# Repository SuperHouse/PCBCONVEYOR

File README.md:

PCB Conveyor Belt
=================

Copyright 2021 SuperHouse Automation Pty Ltd  www.superhouse.tv

THIS IS VERY PRELIMINARY! I'm adding this work-in-progress to GitHub
so that Seon can access it, but it's not in a ready state for
general consumption.
^^^^^^^^^^^^^^^^^^^^^^^^^^^^^^^^^^^^^^^^^^^^^^^^^^^^^^^^^^^^^^^

A conveyor belt for linking together PCB assembly machines, including
pick-and-place, reflow, optical inspection, etc.

The width of the belt is adjustable to suit different sizes of PCBs
and panels. This project includes the design for the mechanical
structure, a controller, and firmware for the controller.

More information:

  http://www.superhouse.tv/pcbconveyor

INSTALLATION
------------
The "Hardware" directory contains the PCB design as an EAGLE project.
This can be imported into KiCAD, or opened natively using Fusion360.

CREDITS
-------
Designed by Jonathan Oxer jon@oxer.com.au

DISTRIBUTION
------------
The specific terms of distribution of this project are governed by the
license referenced below.

LICENSE
-------
Licensed under the TAPR Open Hardware License (www.tapr.org/OHL).
The "license" folder within this repository also contains a copy of
this license in plain text format.

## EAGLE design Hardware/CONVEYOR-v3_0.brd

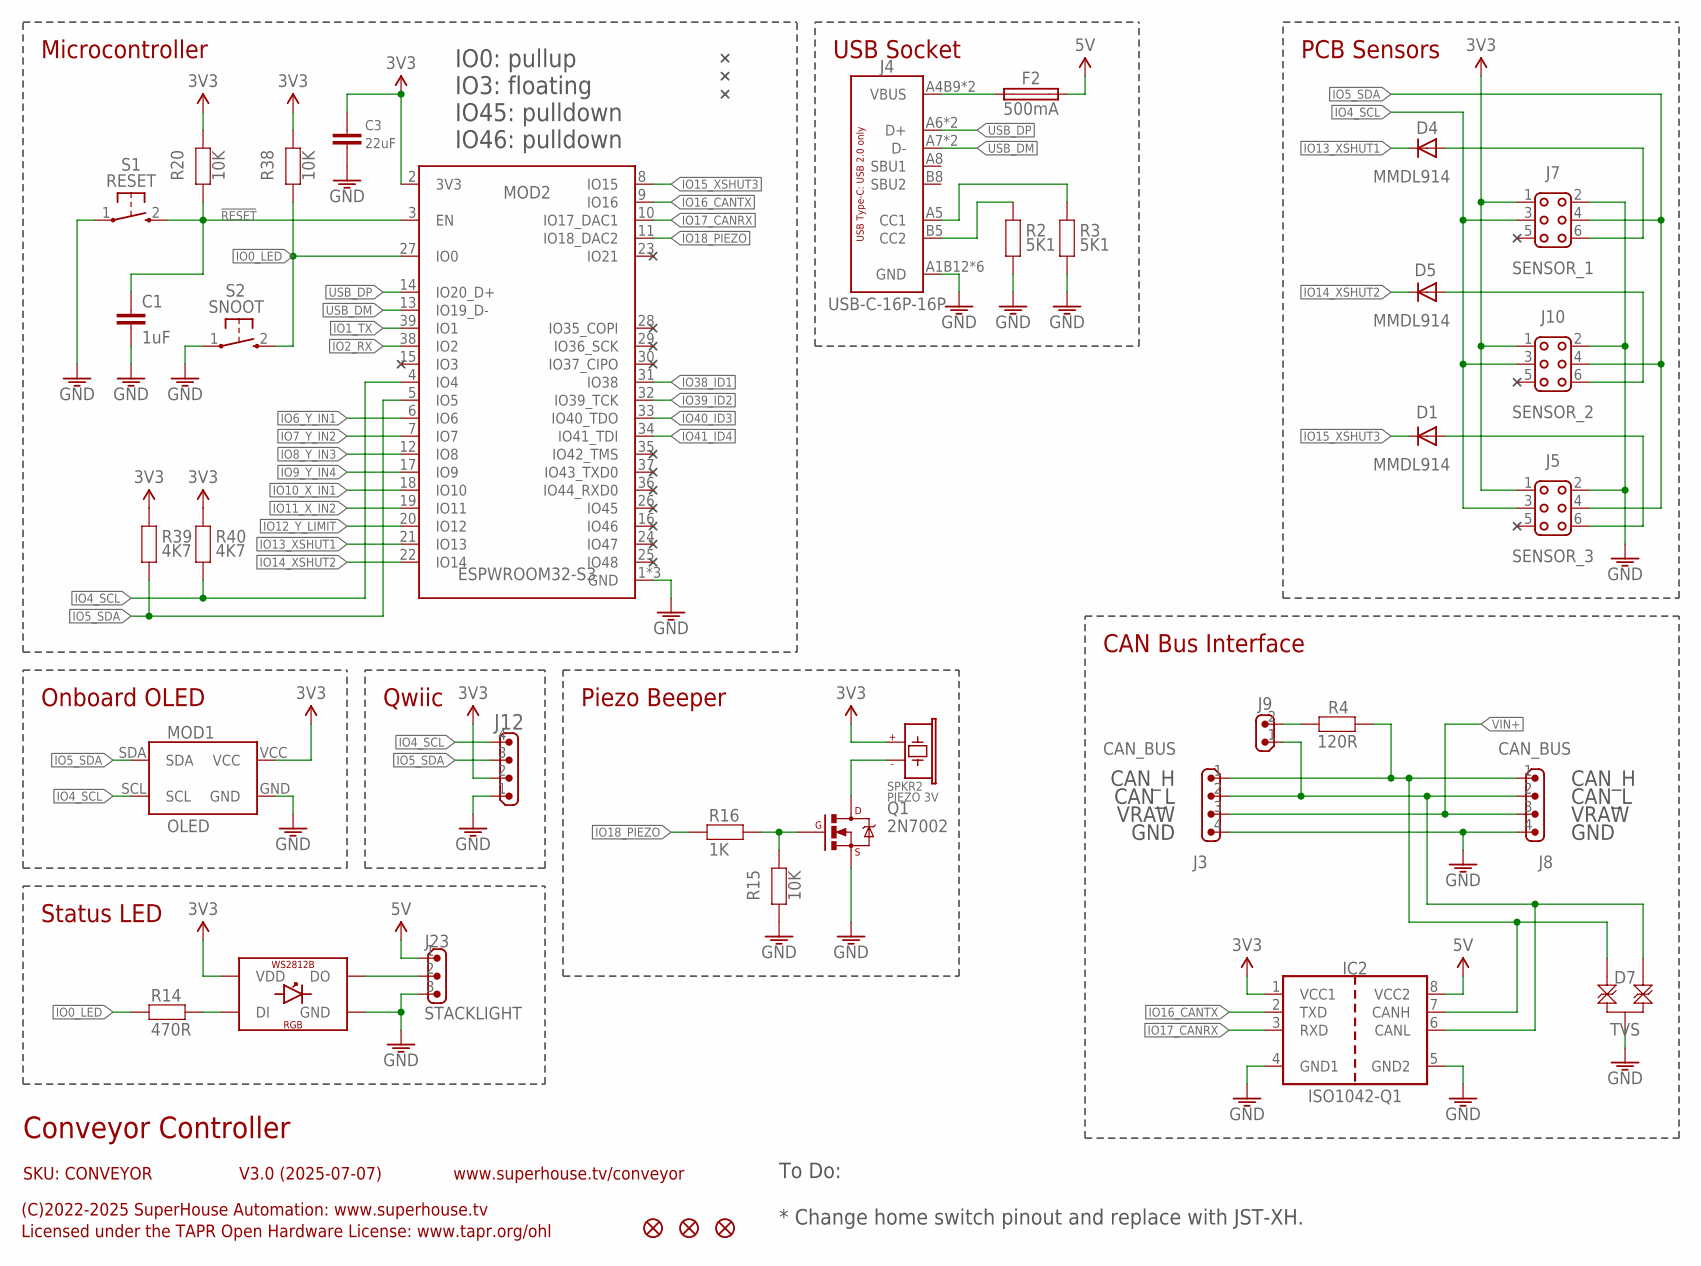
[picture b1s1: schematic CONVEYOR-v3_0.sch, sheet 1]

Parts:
C1: 1uF; C0603
C3: 22uF; C0805
D1, D4, D5: MMDL914; SOD-123
D7: TVS; SOT23-3
F2: 500mA; 1206
IC2: ISO1042-Q1; SO08-W
J3, J8: CAN_BUS; SCREWTERMINAL-3.81MM-PLUGGABLE-HOR-4
J4: USB-C-16P-16P; USB-C-16P
J5: SENSOR_3; 2X3-2.54-SHROUDED
J7: SENSOR_1; 2X3-2.54-SHROUDED
J9: M02-PIN-JUMP-Y; 1X02-P-JUMP-Y
J10: SENSOR_2; 2X3-2.54-SHROUDED
J12: M04-SM4B-SH; JST-SM4B-SH
J23: STACKLIGHT; 1X03
LED2: WS2812B-PTH5MM; 5MM4PIN
MOD1: OLED; OLED-128X32-0.91-HEADER
MOD2: ESPWROOM32-S3
Q1: 2N7002; SOT23-3
R2, R3: 5K1; R0603
R4: 120R; R2010
R14: 470R; R0603
R15, R20, R38: 10K; R0603
R16: 1K; R0603
R39, R40: 4K7; R0603
S1: RESET; TACTILE_SMT_3X4X2
S2: SNOOT; TACTILE_SMT_3X4X2
SPKR2: PIEZO 3V; PIEZO-9.6X9.6-SMT
U$4, U$5, U$6: FIDUCIAL1X2.5; FIDUCIAL-1X2.5

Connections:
3.3V: C3.1, IC2.1 (VCC1), J5.1, J7.1, J10.1, J12.2, LED2.2 (VDD), MOD1.VCC, MOD2.2 (3V3), R20.1, R38.1, R39.1, R40.1, SPKR2.1 (+); also elsewhere on the board
5V: F2.2, IC2.8 (VCC2), J23.1; also elsewhere on the board
!RESET: C1.1, MOD2.3 (EN), R20.2, S1.2 (S)
CAN_H1: D7.2, IC2.7 (CANH), J3.1, J8.1, R4.2
CAN_L1: D7.1, IC2.6 (CANL), J3.2, J8.2, J9.1
GND: C1.2, C3.2, D7.3, IC2.4 (GND1), IC2.5 (GND2), J3.4, J4.A1B12 (GND), J4.A12B1 (GND), J4.FIX1 (GND), J4.FIX2 (GND), J4.FIX3 (GND), J4.FIX4 (GND), J5.2, J7.2, J8.4, J10.2, J12.1, J23.3, LED2.3 (GND), MOD1.GND, MOD2.1 (GND), MOD2.40 (GND), MOD2.41 (GND), Q1.2 (S), R2.2, R3.2, R15.2, S1.1, S2.1; also elsewhere on the board
IO0_LED: MOD2.27 (IO0), R14.1, R38.2, S2.2 (S)
IO1_TX: MOD2.39 (IO1)
IO2_RX: MOD2.38 (IO2)
IO4_SCL: J5.3, J7.3, J10.3, J12.4, MOD1.SCL, MOD2.4 (IO4), R40.2
IO5_SDA: J5.4, J7.4, J10.4, J12.3, MOD1.SDA, MOD2.5 (IO5), R39.2
IO6_Y_IN1: MOD2.6 (IO6); also elsewhere on the board
IO7_Y_IN2: MOD2.7 (IO7); also elsewhere on the board
IO8_Y_IN3: MOD2.12 (IO8); also elsewhere on the board
IO9_Y_IN4: MOD2.17 (IO9); also elsewhere on the board
IO10_X_IN1: MOD2.18 (IO10); also elsewhere on the board
IO11_X_IN2: MOD2.19 (IO11); also elsewhere on the board
IO12_Y_LIMIT: MOD2.20 (IO12); also elsewhere on the board
IO13_XSHUT1: D4.1 (C), MOD2.21 (IO13)
IO14_XSHUT2: D5.1 (C), MOD2.22 (IO14)
IO15_XSHUT3: D1.1 (C), MOD2.8 (IO15)
IO16_CANTX: IC2.2 (TXD), MOD2.9 (IO16)
IO17_CANRX: IC2.3 (RXD), MOD2.10 (IO17_DAC1)
IO18_PIEZO: MOD2.11 (IO18_DAC2), R16.1
IO38_ID1: MOD2.31 (IO38); also elsewhere on the board
IO39_ID2: MOD2.32 (IO39_TCK); also elsewhere on the board
IO40_ID3: MOD2.33 (IO40_TDO); also elsewhere on the board
IO41_ID4: MOD2.34 (IO41_TDI); also elsewhere on the board
IO46: MOD2.16 (IO46)
unnamed: J9.2, R4.1
unnamed: LED2.4 (DI), R14.2
unnamed: D1.2 (A), J5.6
unnamed: J4.B5 (CC2), R2.1
unnamed: J4.A5 (CC1), R3.1
unnamed: F2.1, J4.A4B9 (VBUS), J4.A9B4 (VBUS)
unnamed: J23.2, LED2.1 (DO)
unnamed: D5.2 (A), J10.6
unnamed: Q1.1 (G), R15.1, R16.2
unnamed: Q1.3 (D), SPKR2.2 (-)
unnamed: D4.2 (A), J7.6
USB_DM: J4.A7 (D-), J4.B7 (D-), MOD2.13 (IO19_D-)
USB_DP: J4.A6 (D+), J4.B6 (D+), MOD2.14 (IO20_D+)
VIN+: J3.3, J8.3; also elsewhere on the board

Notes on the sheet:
Conveyor Controller
SKU: CONVEYOR
(C)2022-2025 SuperHouse Automation: www.superhouse.tv
Licensed under the TAPR Open Hardware License: www.tapr.org/ohl
www.superhouse.tv/conveyor
V3.0 (2025-07-07)
To Do: * Change home switch pinout and replace with JST-XH.
Piezo Beeper
Microcontroller
Qwiic
IO0: pullup IO3: floating IO45: pulldown IO46: pulldown
Status LED
PCB Sensors
Onboard OLED
USB Socket
CAN Bus Interface
CAN_H
CAN_L
GND
VRAW

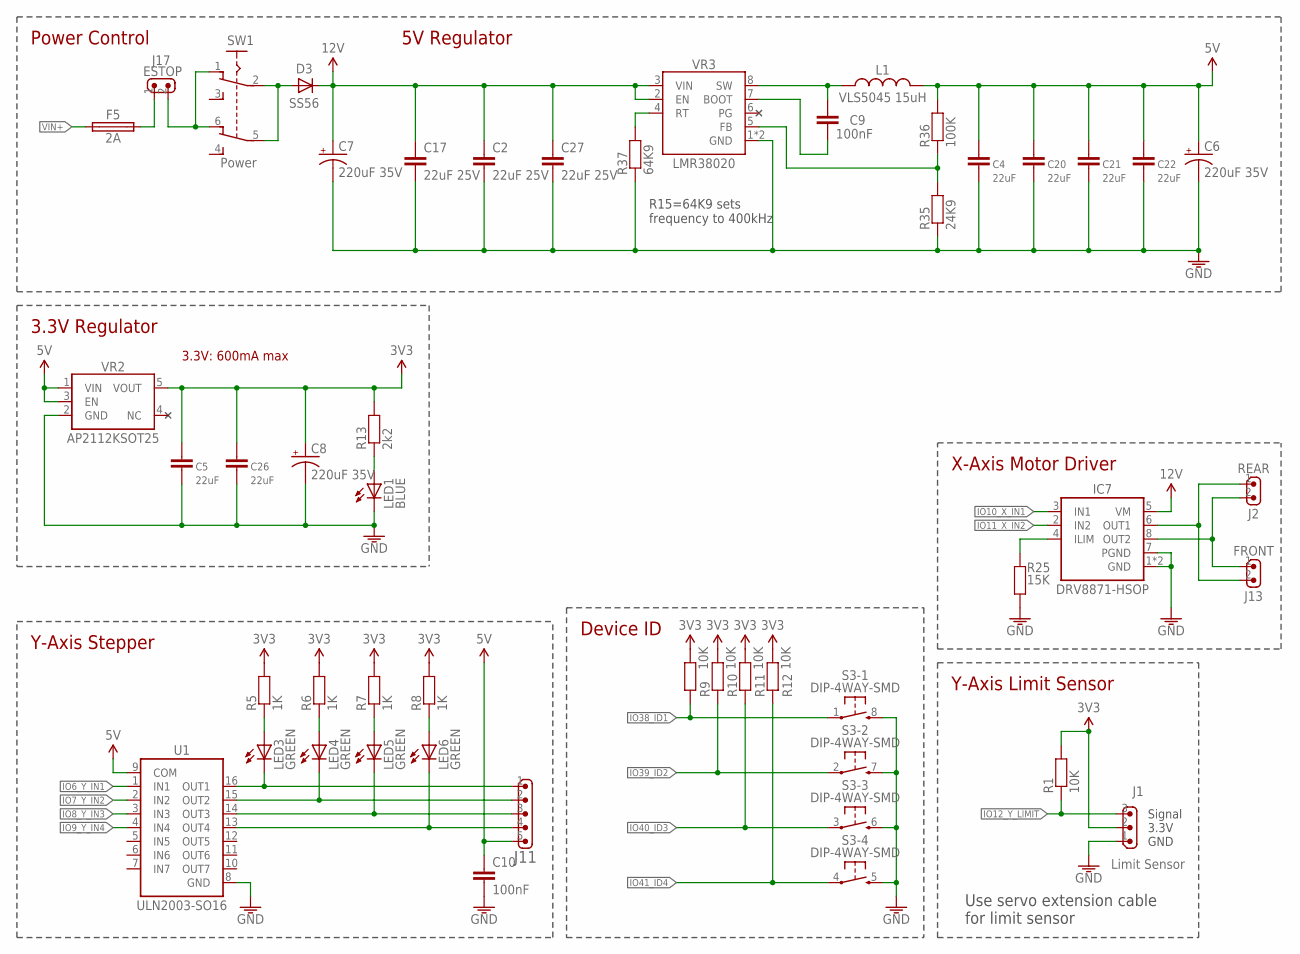
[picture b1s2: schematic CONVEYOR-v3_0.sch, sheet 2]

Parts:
C2, C17, C27: 22uF 25V; C0805
C4, C5, C20, C21, C22, C26: 22uF; C0805
C6, C7, C8: 220uF 35V; PANASONIC_G
C9, C10: 100nF; C0603
D3: SS56; SMA-DIODE
F5: 2A; OMNIBLOK
IC7: DRV8871-HSOP; SOIC8T
J1: Limit Sensor; 1X03-P
J2: REAR; JST-B2B-XH-A
J11: M05-B5B-XH; JST-B5B-XH-A
J13: FRONT; JST-B2B-XH-A
J17: ESTOP; SCREWTERMINAL-3.81MM-PLUGGABLE-HOR-2
L1: VLS5045 15uH; INDUCTOR-5045
LED1: BLUE; LED-0603
LED3, LED4, LED5, LED6: GREEN; LED-0603
R1, R9, R10, R11, R12: 10K; R0603
R5, R6, R7, R8: 1K; R0603
R13: 2k2; R0603
R25: 15K; R0603
R35: 24K9; R0603
R36: 100K; R0603
R37: 64K9; R0603
S3: DIP-4WAY-SMD; DIP-8-SMD
SW1: Power; 7201SD9AV2BE
U1: ULN2003-SO16; SO16
VR2: AP2112KSOT25; SOT23-5
VR3: LMR38020; HSOIC8

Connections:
3.3V: C5.1, C8.+, C26.1, J1.2, R1.2, R5.2, R6.2, R7.2, R8.2, R9.2, R10.2, R11.2, R12.2, R13.2, VR2.5 (VOUT); also elsewhere on the board
5V: C4.1, C6.+, C10.1, C20.1, C21.1, C22.1, J11.5, L1.2, R36.2, U1.9 (COM), VR2.1 (VIN), VR2.3 (EN); also elsewhere on the board
12V: C2.1, C7.+, C17.1, C27.1, D3.C, IC7.5 (VM), VR3.2 (EN), VR3.3 (VIN)
GND: C2.2, C4.2, C5.2, C6.-, C7.-, C8.-, C10.2, C17.2, C20.2, C21.2, C22.2, C26.2, C27.2, IC7.1 (GND), IC7.7 (PGND), IC7.TGND (GND), J1.1, LED1.C, R25.1, R35.1, R37.1, S3.5 (S), S3.6 (S), S3.7 (S), S3.8 (S), U1.8 (GND), VR2.2 (GND), VR3.1 (GND), VR3.TGND (GND); also elsewhere on the board
IO6_Y_IN1: U1.1 (IN1); also elsewhere on the board
IO7_Y_IN2: U1.2 (IN2); also elsewhere on the board
IO8_Y_IN3: U1.3 (IN3); also elsewhere on the board
IO9_Y_IN4: U1.4 (IN4); also elsewhere on the board
IO10_X_IN1: IC7.3 (IN1); also elsewhere on the board
IO11_X_IN2: IC7.2 (IN2); also elsewhere on the board
IO12_Y_LIMIT: J1.3, R1.1; also elsewhere on the board
IO38_ID1: R9.1, S3.1; also elsewhere on the board
IO39_ID2: R10.1, S3.2; also elsewhere on the board
IO40_ID3: R11.1, S3.3; also elsewhere on the board
IO41_ID4: R12.1, S3.4; also elsewhere on the board
unnamed: J17.2, SW1.1, SW1.6
unnamed: IC7.4 (ILIM), R25.2
unnamed: F5.2, J17.1
unnamed: D3.A, SW1.2, SW1.5
unnamed: LED3.A, R5.1
unnamed: J11.1, LED3.C, U1.16 (OUT1)
unnamed: LED4.A, R6.1
unnamed: LED5.A, R7.1
unnamed: LED6.A, R8.1
unnamed: J11.2, LED4.C, U1.15 (OUT2)
unnamed: J11.3, LED5.C, U1.14 (OUT3)
unnamed: J11.4, LED6.C, U1.13 (OUT4)
unnamed: IC7.6 (OUT1), J2.1, J13.2
unnamed: IC7.8 (OUT2), J2.2, J13.1
unnamed: LED1.A, R13.1
unnamed: C9.1, L1.1, VR3.8 (SW)
unnamed: R37.2, VR3.4 (RT)
unnamed: R35.2, R36.1, VR3.5 (FB)
unnamed: C9.2, VR3.7 (BOOT)
PG: VR3.6 (PG)
VIN+: F5.1; also elsewhere on the board

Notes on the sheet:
3.3V: 600mA max
5V Regulator
3.3V Regulator
R15=64K9 sets frequency to 400kHz
Power Control
Y-Axis Stepper
Device ID
3.3V
Signal
GND
Use servo extension cable for limit sensor
Y-Axis Limit Sensor
X-Axis Motor Driver

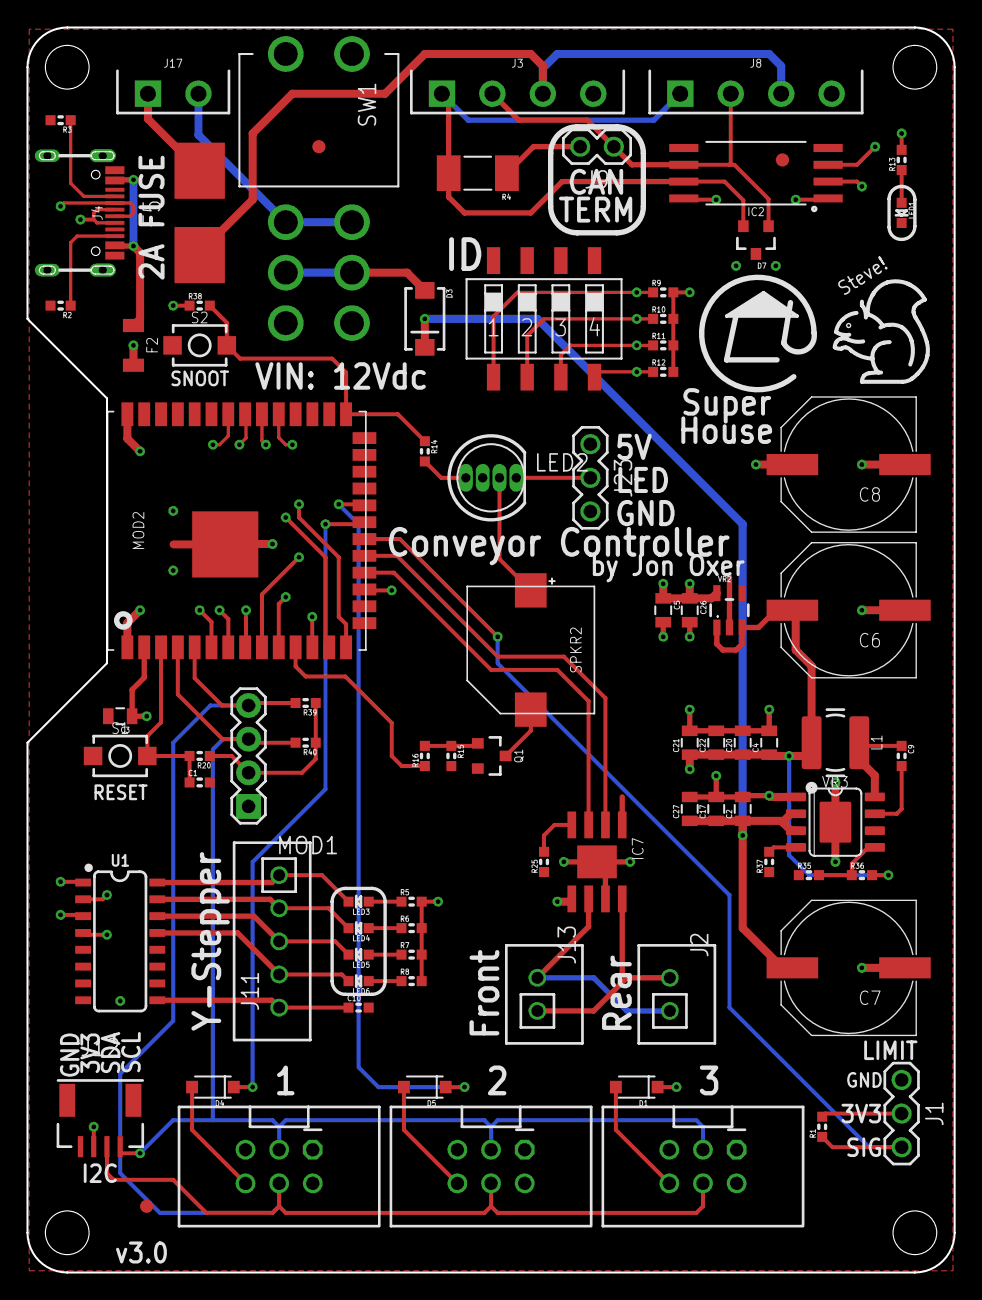
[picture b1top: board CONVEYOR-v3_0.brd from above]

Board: 4 copper layers, 70.0 x 94.0 mm, 84 parts (0 on the bottom side), 60 nets.

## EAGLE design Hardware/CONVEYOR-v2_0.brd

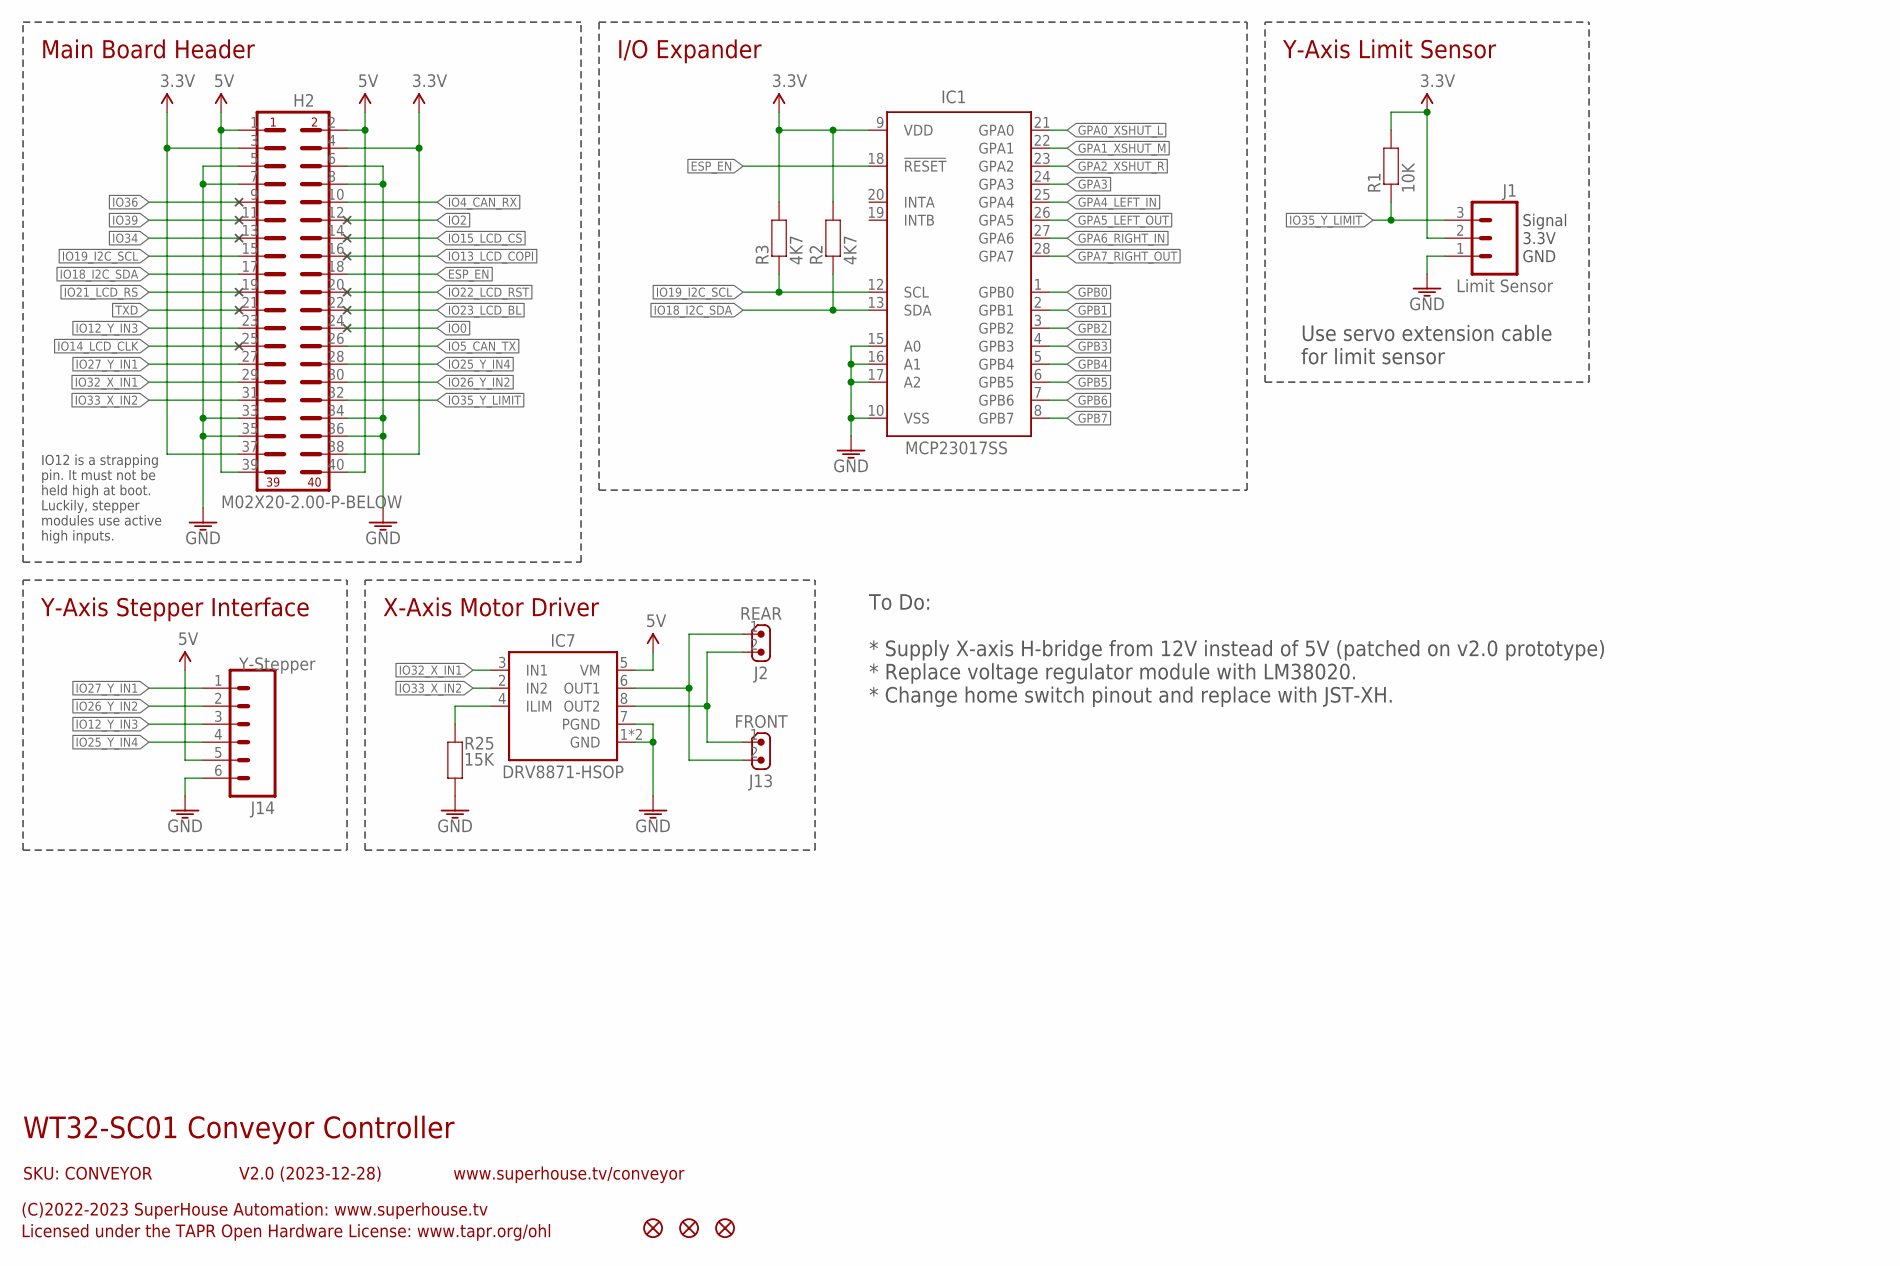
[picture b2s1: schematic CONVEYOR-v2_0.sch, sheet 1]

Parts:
H2: M02X20-2.00-P-BELOW; 2X20-2.00-P-BELOW
IC1: MCP23017SS; SSOP28
IC7: DRV8871-HSOP; SOIC8T
J1: Limit Sensor; 1X03-P
J2: REAR; JST-B2B-XH-A
J13: FRONT; JST-B2B-XH-A
J14: Y-Stepper; JST-B6B-XH-A
R1: 10K; R0603
R2, R3: 4K7; R0603
R25: 15K; R0603
U$4, U$5, U$6: FIDUCIAL1X2.5; FIDUCIAL-1X2.5

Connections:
3.3V: H2.3, H2.4, H2.37, H2.38, IC1.9 (VDD), J1.2, R1.2, R2.2, R3.2; also elsewhere on the board
5V: H2.1, H2.2, H2.39, H2.40, IC7.5 (VM), J14.5; also elsewhere on the board
ESP_EN: H2.18, IC1.18 (!RESET)
GND: H2.5, H2.6, H2.7, H2.8, H2.33, H2.34, H2.35, H2.36, IC1.10 (VSS), IC1.15 (A0), IC1.16 (A1), IC1.17 (A2), IC7.1 (GND), IC7.7 (PGND), IC7.TGND (GND), J1.1, J14.6, R25.1; also elsewhere on the board
GPA0_XSHUT_L: IC1.21 (GPA0); also elsewhere on the board
GPA1_XSHUT_M: IC1.22 (GPA1); also elsewhere on the board
GPA2_XSHUT_R: IC1.23 (GPA2); also elsewhere on the board
GPA3: IC1.24 (GPA3)
GPA4_LEFT_IN: IC1.25 (GPA4); also elsewhere on the board
GPA5_LEFT_OUT: IC1.26 (GPA5); also elsewhere on the board
GPA6_RIGHT_IN: IC1.27 (GPA6); also elsewhere on the board
GPA7_RIGHT_OUT: IC1.28 (GPA7); also elsewhere on the board
GPB0: IC1.1 (GPB0)
GPB1: IC1.2 (GPB1)
GPB2: IC1.3 (GPB2)
GPB3: IC1.4 (GPB3)
GPB4: IC1.5 (GPB4)
GPB5: IC1.6 (GPB5)
GPB6: IC1.7 (GPB6)
GPB7: IC1.8 (GPB7)
IO0: H2.24
IO2: H2.12
IO4_CAN_RX: H2.10; also elsewhere on the board
IO5_CAN_TX: H2.26; also elsewhere on the board
IO12_Y_IN3: H2.23, J14.3
IO13_LCD_COPI: H2.16
IO14_LCD_CLK: H2.25
IO15_LCD_CS: H2.14
IO18_I2C_SDA: H2.17, IC1.13 (SDA), R2.1; also elsewhere on the board
IO19_I2C_SCL: H2.15, IC1.12 (SCL), R3.1; also elsewhere on the board
IO21_LCD_RS: H2.19
IO22_LCD_RST: H2.20
IO23_LCD_BL: H2.22
IO25_Y_IN4: H2.28, J14.4
IO26_Y_IN2: H2.30, J14.2
IO27_Y_IN1: H2.27, J14.1
IO32_X_IN1: H2.29, IC7.3 (IN1)
IO33_X_IN2: H2.31, IC7.2 (IN2)
IO34: H2.13
IO35_Y_LIMIT: H2.32, J1.3, R1.1
IO36: H2.9
IO39: H2.11
unnamed: IC7.4 (ILIM), R25.2
unnamed: IC7.6 (OUT1), J2.1, J13.2
unnamed: IC7.8 (OUT2), J2.2, J13.1
TXD: H2.21

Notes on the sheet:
WT32-SC01 Conveyor Controller
SKU: CONVEYOR
(C)2022-2023 SuperHouse Automation: www.superhouse.tv
Licensed under the TAPR Open Hardware License: www.tapr.org/ohl
www.superhouse.tv/conveyor
V2.0 (2023-12-28)
Y-Axis Stepper Interface
Main Board Header
I/O Expander
3.3V
Signal
GND
Use servo extension cable for limit sensor
Y-Axis Limit Sensor
IO12 is a strapping pin. It must not be held high at boot. Luckily, stepper modules use active high inputs.
X-Axis Motor Driver
To Do: * Supply X-axis H-bridge from 12V instead of 5V (patched on v2.0 prototype) * Replace voltage regulator module with LM38020. * Change home switch pinout and replace with JST-XH.

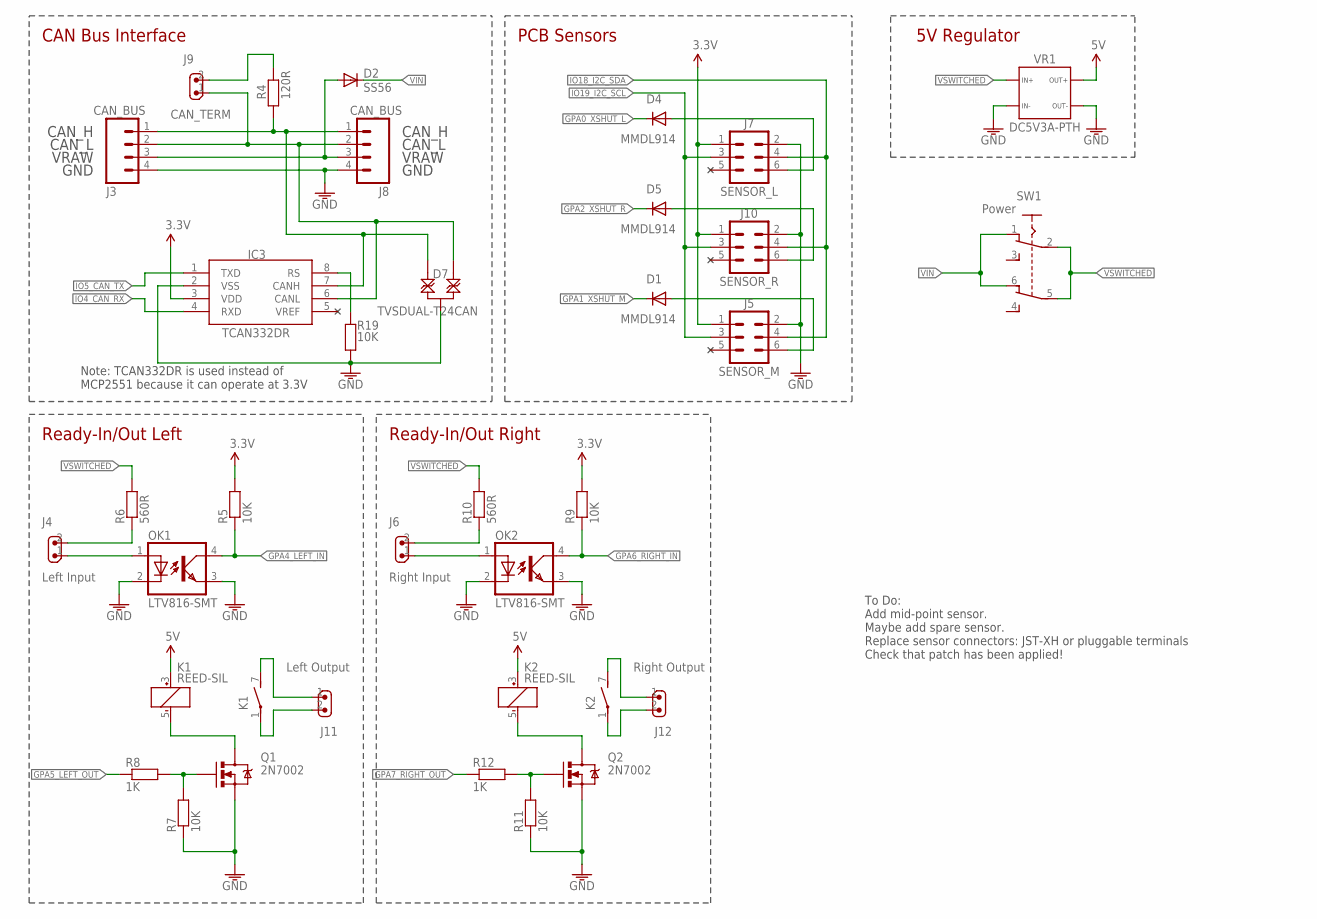
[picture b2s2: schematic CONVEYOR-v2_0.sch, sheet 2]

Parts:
D1, D4, D5: MMDL914; SOD-323
D2: SS56; SMA-DIODE
D7: TVSDUAL-T24CAN; SOT23-3
IC3: TCAN332DR; SO08
J3, J8: CAN_BUS; SCREWTERMINAL-3.81MM-VERT-4
J4: Left Input; 1X02-KF2510
J5: SENSOR_M; 2X3-2.54-SHROUDED
J6: Right Input; 1X02-KF2510
J7: SENSOR_L; 2X3-2.54-SHROUDED
J9: CAN_TERM; 1X02-P-JUMP-Y
J10: SENSOR_R; 2X3-2.54-SHROUDED
J11: Left Output; 1X02-KF2510
J12: Right Output; 1X02-KF2510
K1, K2: REED-SIL; REED
OK1, OK2: LTV816-SMT; SMD4
Q1, Q2: 2N7002; SOT23-3
R4: 120R; R2010
R5, R7, R9, R11, R19: 10K; R0603
R6, R10: 560R; R0603
R8, R12: 1K; R0603
SW1: Power; 7201SD9AV2BE
VR1: DC5V3A-PTH

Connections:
3.3V: IC3.3 (VDD), J5.1, J7.1, J10.1, R5.2, R9.2; also elsewhere on the board
5V: K1.3 (+), K2.3 (+), VR1.3A (3), VR1.3B (3); also elsewhere on the board
CAN_H1: D7.2, IC3.7 (CANH), J3.1, J8.1, R4.1
CAN_L1: D7.1, IC3.6 (CANL), J3.2, J8.2, J9.1
CAN_VIN: D2.A, J3.3, J8.3
GND: D7.3, IC3.2 (VSS), J3.4, J5.2, J7.2, J8.4, J10.2, OK1.2 (C), OK1.3 (EMIT), OK2.2 (C), OK2.3 (EMIT), Q1.2 (S), Q2.2 (S), R7.1, R11.1, R19.1, VR1.1A (1), VR1.1B (1), VR1.4A (4), VR1.4B (4); also elsewhere on the board
GPA0_XSHUT_L: D4.1 (C); also elsewhere on the board
GPA1_XSHUT_M: D1.1 (C); also elsewhere on the board
GPA2_XSHUT_R: D5.1 (C); also elsewhere on the board
GPA4_LEFT_IN: OK1.4 (COL), R5.1; also elsewhere on the board
GPA5_LEFT_OUT: R8.1; also elsewhere on the board
GPA6_RIGHT_IN: OK2.4 (COL), R9.1; also elsewhere on the board
GPA7_RIGHT_OUT: R12.1; also elsewhere on the board
IO4_CAN_RX: IC3.4 (RXD); also elsewhere on the board
IO5_CAN_TX: IC3.1 (TXD); also elsewhere on the board
IO18_I2C_SDA: J5.4, J7.4, J10.4; also elsewhere on the board
IO19_I2C_SCL: J5.3, J7.3, J10.3; also elsewhere on the board
unnamed: IC3.8 (RS), R19.2
unnamed: D1.2 (A), J5.6
unnamed: J9.2, R4.2
unnamed: D5.2 (A), J10.6
unnamed: J4.1, OK1.1 (A)
unnamed: J4.2, R6.1
unnamed: D4.2 (A), J7.6
unnamed: K1.5 (-), Q1.3 (D)
unnamed: J11.2, K1.1
unnamed: Q1.1 (G), R7.2, R8.2
unnamed: J11.1, K1.7 (S)
unnamed: Q2.1 (G), R11.2, R12.2
unnamed: K2.5 (-), Q2.3 (D)
unnamed: J12.2, K2.1
unnamed: J12.1, K2.7 (S)
unnamed: J6.1, OK2.1 (A)
unnamed: J6.2, R10.1
VIN: D2.C, SW1.1, SW1.6
VSWITCHED: R6.2, R10.2, SW1.2, SW1.5, VR1.2A (2), VR1.2B (2)

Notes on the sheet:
5V Regulator
CAN Bus Interface
Note: TCAN332DR is used instead of MCP2551 because it can operate at 3.3V
CAN_H
CAN_L
GND
VRAW
PCB Sensors
Ready-In/Out Left
Ready-In/Out Right
To Do: Add mid-point sensor. Maybe add spare sensor. Replace sensor connectors: JST-XH or pluggable terminals Check that patch has been applied!

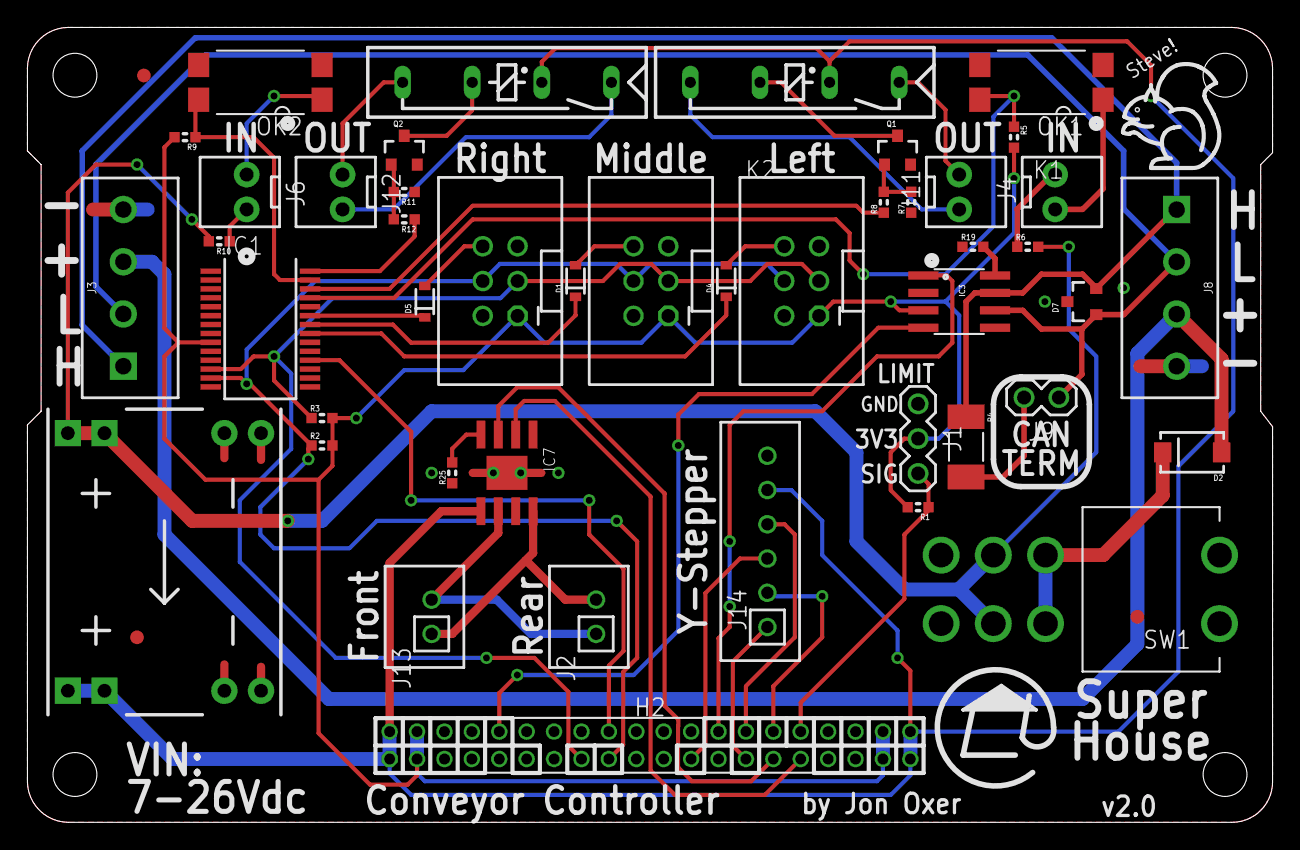
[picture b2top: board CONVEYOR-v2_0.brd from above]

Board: 2 copper layers, 90.9 x 58.0 mm, 48 parts (0 on the bottom side), 47 nets.

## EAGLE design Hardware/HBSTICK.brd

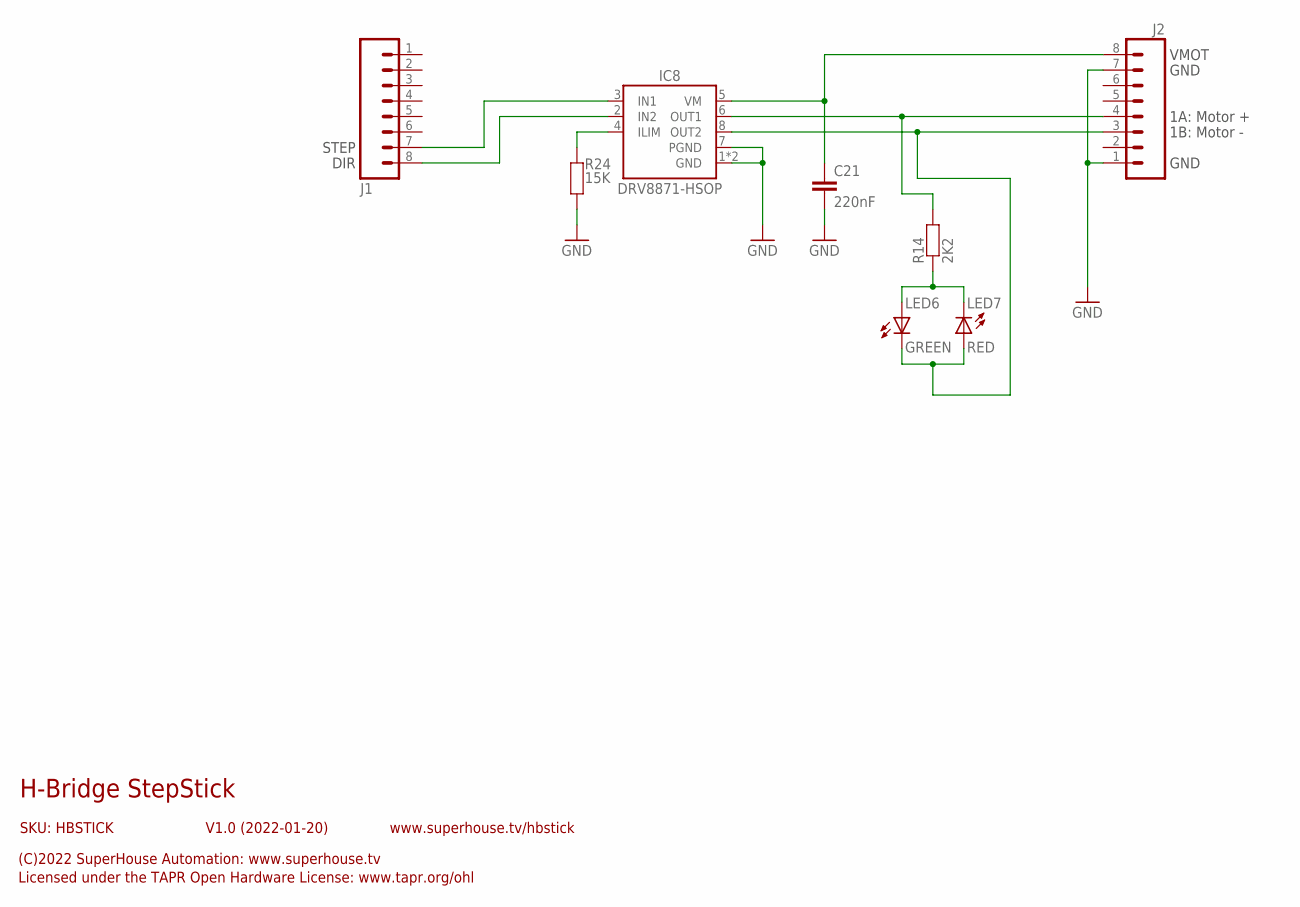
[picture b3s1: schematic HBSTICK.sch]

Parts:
C21: 220nF; C0603
IC8: DRV8871-HSOP; SOIC8T
J1, J2: M08-PIN-BELOW; 1X08-P-BELOW
LED6: GREEN; LED-0603
LED7: RED; LED-0603
R14: 2K2; R0603
R24: 15K; R0603

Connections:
GND: C21.2, IC8.1 (GND), IC8.7 (PGND), IC8.TGND (GND), J2.1, J2.7, R24.1
MOTOR+: IC8.6 (OUT1), J2.4, R14.2
MOTOR-: IC8.8 (OUT2), J2.3, LED6.C, LED7.A
unnamed: IC8.2 (IN2), J1.8
unnamed: IC8.3 (IN1), J1.7
unnamed: LED6.A, LED7.C, R14.1
unnamed: IC8.4 (ILIM), R24.2
VIN+: C21.1, IC8.5 (VM), J2.8

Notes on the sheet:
H-Bridge StepStick
SKU: HBSTICK
(C)2022 SuperHouse Automation: www.superhouse.tv
Licensed under the TAPR Open Hardware License: www.tapr.org/ohl
www.superhouse.tv/hbstick
V1.0 (2022-01-20)
VMOT
GND
1A: Motor +
1B: Motor -
STEP
DIR

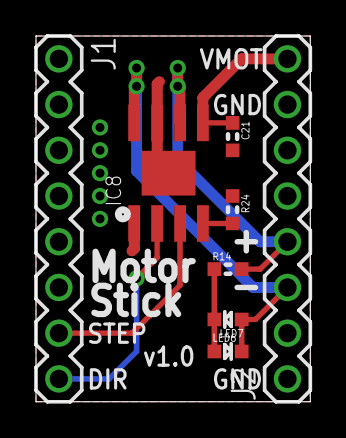
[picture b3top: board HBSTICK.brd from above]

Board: 2 copper layers, 15.2 x 20.3 mm, 8 parts (0 on the bottom side), 8 nets.

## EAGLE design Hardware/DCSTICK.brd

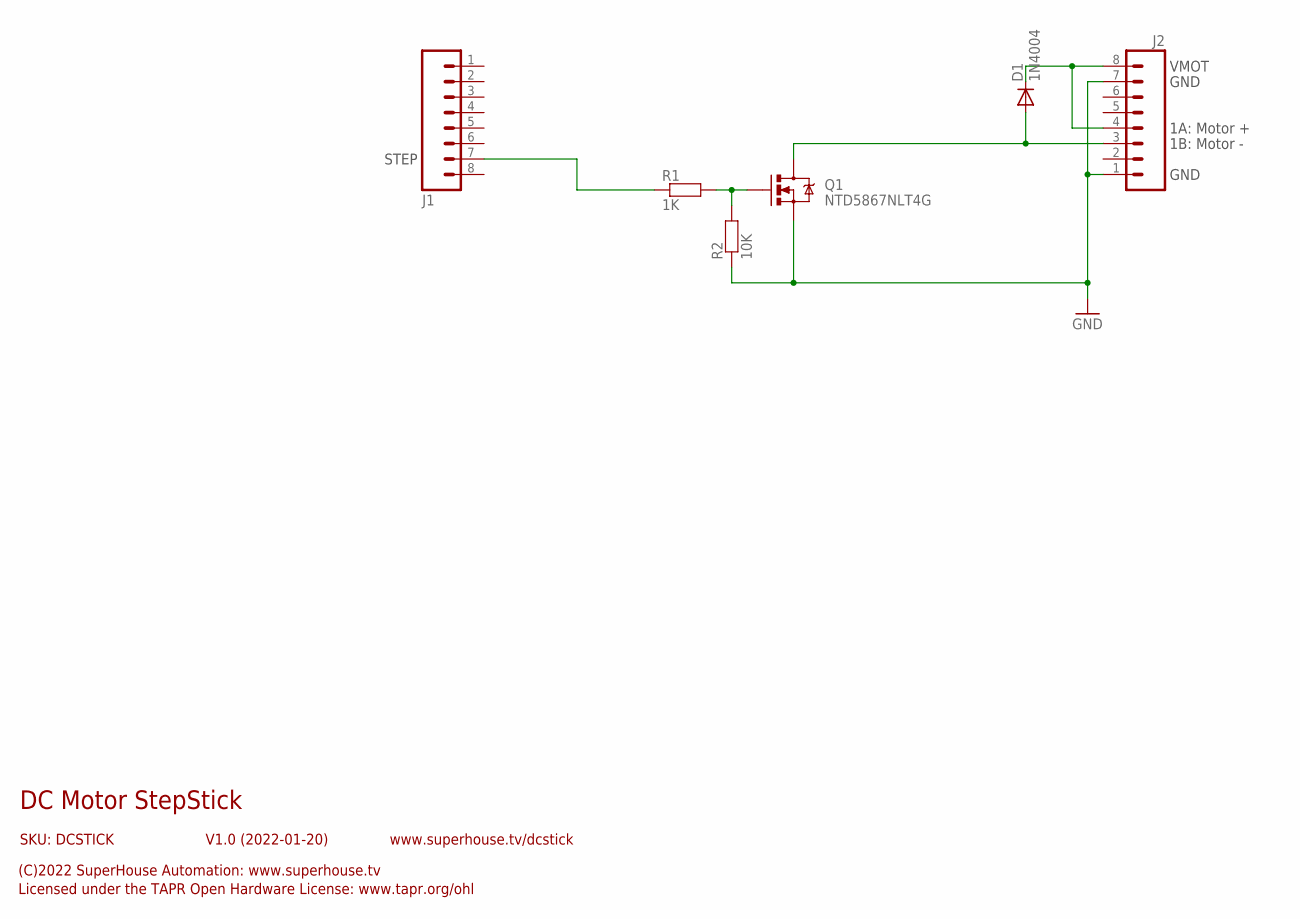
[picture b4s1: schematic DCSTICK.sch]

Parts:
D1: 1N4004; SMA-DIODE
J1, J2: M08-PIN-BELOW; 1X08-P-BELOW
Q1: NTD5867NLT4G; DPACK
R1: 1K; R0603
R2: 10K; R0603

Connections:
GND: J2.1, J2.7, Q1.3 (S), R2.1
unnamed: J1.7, R1.1
unnamed: Q1.1 (G), R1.2, R2.2
unnamed: D1.C, J2.4, J2.8
unnamed: D1.A, J2.3, Q1.2 (D)

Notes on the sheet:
DC Motor StepStick
SKU: DCSTICK
(C)2022 SuperHouse Automation: www.superhouse.tv
Licensed under the TAPR Open Hardware License: www.tapr.org/ohl
www.superhouse.tv/dcstick
V1.0 (2022-01-20)
VMOT
GND
1A: Motor +
1B: Motor -
STEP

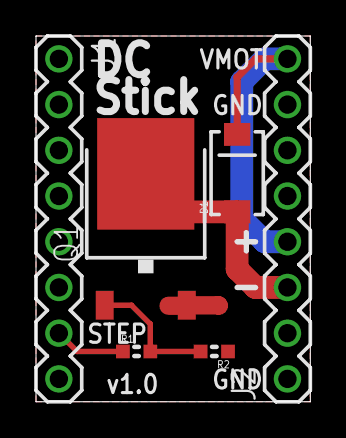
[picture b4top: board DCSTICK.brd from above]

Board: 2 copper layers, 15.2 x 20.3 mm, 6 parts (0 on the bottom side), 5 nets.

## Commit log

2021-12-23 Initial project import
2022-12-20 v1.0 release.
2022-12-20 Added Stepstick format board with N-MOSFET for simple DC drive.
2022-12-20 Added Stepstick format board with H-Bridge for bidirectional DC motor drive.
2022-12-20 Added controller pinout spreadsheet.
2022-12-20 Added images.
2022-12-20 Added 3D files for some mechanical parts.
2022-12-20 Added SMEMA interface standard.
2022-12-20 Formatting
2025-03-30 Added in-progress firmware for v2 hardware
2025-03-30 Added gitignore
2025-03-30 Added 3D models for most printable parts.
2025-03-31 Defined command codes for various operations. Implemented time-based unload. Added timeout to movement operations.
2025-04-01 Changed timed-dispense mode to queue the next board at the end of the conveyor. Added time reporting to state change debugging.
2025-05-04 Added v2.0 schematic and board layout
2025-05-04 Added support for ready-in/out using CAN bus.
2025-11-25 Added v3.0 controller hardware design files.
2025-11-25 Typo in README

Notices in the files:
Hardware/CONVEYOR-v2_0.brd:
Copyright 2022-2023 SuperHouse Automation P/L
Released under the TAPR Open Hardware License
Hardware/CONVEYOR-v3_0.brd:
Copyright 2022-2025 SuperHouse Automation P/L
